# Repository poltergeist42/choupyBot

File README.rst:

=========
choupyBot
=========

   :Autheur:          `Poltergeist42 <https://github.com/poltergeist42>`_
   :Organistation:    `VoLAB <https://github.com/volab>`_
   :Projet:           `choupyBot <https://github.com/volab/choupyBot>`_
   :Licence:          CC BY-NC-SA 4.0
   :Liens:            https://creativecommons.org/licenses/by-nc-sa/4.0/ 

------------------------------------------------------------------------------------------

Description
===========

ChoupyBot est un petit "robot" animé par un Raspberry pi et motoriser par 2 moteurs
pas à pas (PAP) et un capteur ultrason.

L'objectif de ce projet et de réaliser une petite plateforme ludique qui pourra être
programmée / commandée à distance par un enfant. Ce robot évoluera dans un quadrillage
de 15x15.

**N.B :** la dimension des cases sera déterminée ultérieurement en fonction
de la taille du robot.

Voir le doc de conception pour plus de détail :
https://github.com/volab/choupyBot/blob/master/_1_userDoc/choupyBot_doc.rst

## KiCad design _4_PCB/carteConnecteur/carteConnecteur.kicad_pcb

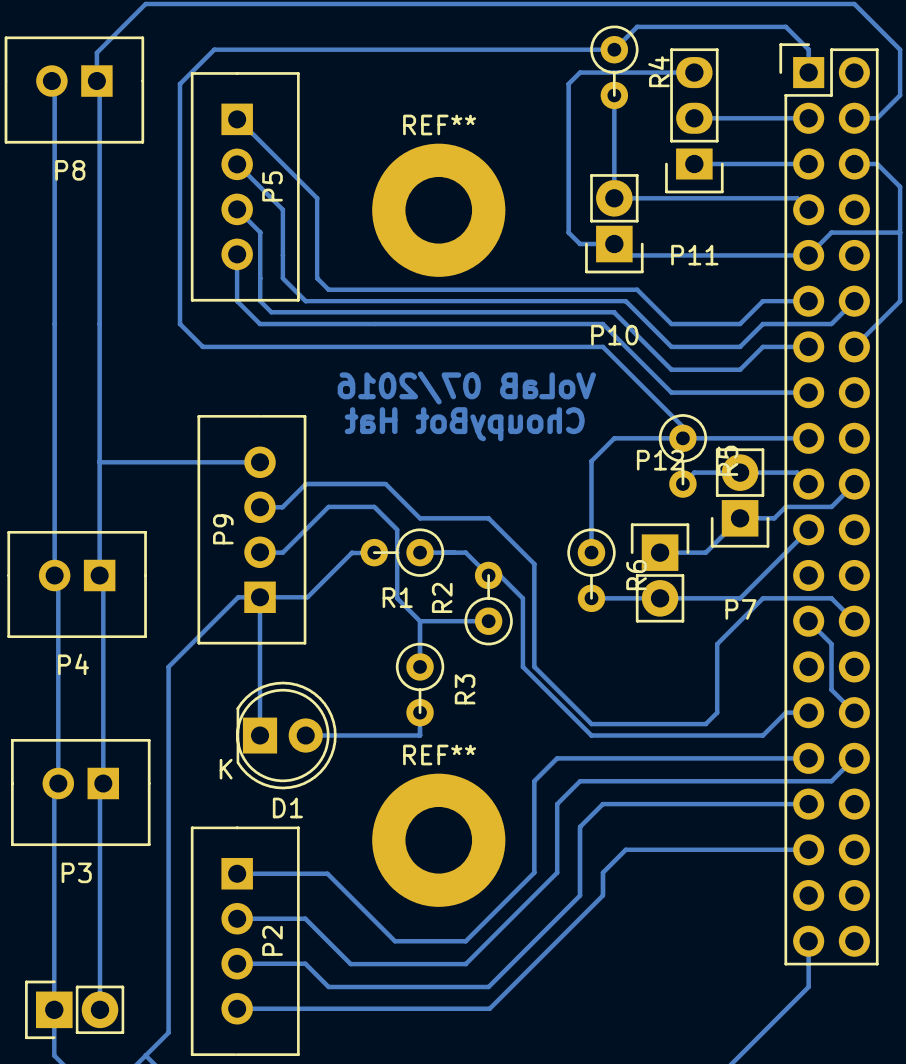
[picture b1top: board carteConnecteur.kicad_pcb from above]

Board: 2 copper layers, 19 parts (0 on the bottom side), 20 nets.

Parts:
D1: LED; LED-5MM
P1: +5 (ubec); Pin_Header_Straight_1x02
P2: PAP_D; XH_connector_4pins_Vert
P3: +5 (pap_G); XH_connector_2pins_Vert
P4: +5 (pap_D); XH_connector_2pins_Vert
P5: PAP_G; XH_connector_4pins_Vert
P6: RPi_Conn; Pin_Header_Straight_2x20
P7: BP1; Pin_Header_Straight_1x02
P8: +5 (RPi); XH_connector_2pins_Vert
P9: HC-SR04; XH_connector_4pins_Vert
P10: N.U; Pin_Header_Straight_1x02
P11: I2c; Pin_Header_Straight_1x03
P12: BP2; Pin_Header_Straight_1x02
R1: 20k; Resistor_Vertical_2-54
R2, R4, R5, R6: 10k; Resistor_Vertical_2-54
R3: 330R; Resistor_Vertical_2-54

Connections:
+3V3: P6.1, P6.17, R4.1, R5.1, R6.1
/Echo: P9.2, R2.1, R3.1
/GPIO04: P6.7, P10.2, R4.2
/GPIO06: P2.1, P6.31
/GPIO12: P2.2, P6.32
/GPIO13: P2.3, P6.33
/GPIO17: P5.1, P6.11
/GPIO18: P5.2, P6.12
/GPIO19: P2.4, P6.35
/GPIO22: P5.4, P6.15
/GPIO27: P5.3, P6.13
/SCL: P6.5, P11.1
/SDA: P6.3, P11.2
/Trig: P6.26, P9.3
GNDPWR: D1.1, P1.1, P3.2, P4.2, P6.6, P6.9, P6.14, P6.20, P6.25, P6.30, P6.39, P7.1, P8.2, P9.1, P10.1, P11.3, P12.1, R1.2
unnamed: D1.2, R3.2
unnamed: P6.19, P7.2, R5.2
unnamed: P6.29, R1.1, R2.2
unnamed: P6.21, P12.2, R6.2
VCC: P1.2, P3.1, P4.1, P6.4, P8.1, P9.4

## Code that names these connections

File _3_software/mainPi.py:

#!/usr/bin/env python
# -*- coding: utf-8 -*-

"""

=========
choupyBot
=========

   :Nom du fichier:     choupyBot.py
   :Autheur:            `Poltergeist42 <https://github.com/poltergeist42>`_
   :Version:            20160731

####

   :Licence:            CC-BY-NC-SA
   :Liens:              https://creativecommons.org/licenses/by-nc-sa/4.0/

####

    :dev language:      Python 3.4
    
####

lexique
=======

   :**v_**:                 variable
   :**l_**:                 list
   :**t_**:                 tuple
   :**d_**:                 dictionnaire
   :**f_**:                 fonction
   :**C_**:                 Class
   :**i_**:                 Instance
   :**m_**:                 Module
"""
try :
    from moteurPap.moteurPap import C_MoteurPap
except ImportError :
    print( "module 'moteurPap' non charge") 

try :
    from ultrason.ultrason import C_ultrasonSensor
except ImportError :
    print( "module 'ultrason' non charge")
    
try :
    from devChk.devChk import C_DebugMsg
except ImportError :
    print( "module 'devChk' non charge")
    
try :
    from objJson.objJson import C_ObjJson
except ImportError :
    print( "module 'objJson' non charge")

class C_choupyBot(object) :
    def __init__(self, ):
        """ variables globales """
        
        ## Creation de l'instance de C_DebugMsg
        self.i_dbg = C_DebugMsg()
        
        ## Variables globales
        self.v_case = 15
        self.v_mode = ""
        
        
        
    def __del__(self) :
        """ Destructor
        
            Permet de fremer proprement l'instance en cours.
            il faut utilise :
            ::
            
                del [nom_de_l'_instance]
                
            N.B : cette methode est appelee automatiquement par le ramasse miette si
            l'instance n'est plus solicitee.
        """
        v_className = self.__class__.__name__
        print("\n\t\tL'instance de la class {} est terminee".format(c_className))

        
    def f_setMode(self, v_mode = "boxxle") :
        """ identification / modification du mode de fonctionnement du robot
        
            Le Robot peut être parametrer pour fonctionner selon plusieur mode.
            
            **Les modes disponibles sont :**
            
                * Boxxle (mode par defaut)
                * Parcours
                * Aventure
        """
        if v_mode == "boxxle" or v_mode == "parcours" or v_mode == "aventure"
            self.v_mode = v_mode
        else : self.v_mode = "boxxle"
        
    def f_papInit(self):
        """ initialisation des 2 moteur pas a pas (pap)
        
            +------------+-------------------------+
            | BCM (GPIO) | Serigraphie sur UNL2003 |
            +============+=========================+
            |   v_gpioA  |           N1            |
            +------------+-------------------------+
            |   v_gpioB  |           N2            |
            +------------+-------------------------+
            |   v_gpioC  |           N3            |
            +------------+-------------------------+
            |   v_gpioD  |           N4            |
            +------------+-------------------------+
           
            le papGauche est intialiser sur les GPIO par defaut soit ::
           
                v_gpioA = GPIO17
                v_gpioB = GPIO18
                v_gpioC = GPIO27
                v_gpioD = GPIO22
           
            et tourne dans le sens anti-horriare.
            le papDroit est initialiser sur un autre jeux de GPIO ::
           
                v_gpioA = GPIO06
                v_gpioB = GPIO12
                v_gpioC = GPIO13
                v_gpioD = GPIO19
                
            et tourne dans le sens horriare. La valeur de v_rayonInit correspond
            au rayon des roues du robot. Les deux pap tournes en sens inverse l'un de 
            l'aure, pour que le robot puisse aller tout droit.
        """
       
        ## papGauche
        self.i_papGauche = C_MoteurPap(v_rotationInit = "antihorraire", v_rayonInit = 3)
        self.i_papGauche.f_gpioInit(v_gpioA=06, v_gpioB=12, v_gpioC=13, v_gpioD=19)
        
        ## papDroit
        self.i_PapDroit  = C_MoteurPap(v_rayonInit = 3)
        self.i_PapDroit.f_gpioInit()

                                        
    def f_sonarInit(self) :
        """ Initialisation du capteur ultrason

        La broche du trig et configuer sur GPIO 7 par défaut.
        La broche echo ayant le GPIO 12 par defaut, elle a ete reconfiguree
        sur GPIO 5
        """
        
        i_ultrason = C_ultrasonSensor()
        i_ultrason.f_ultraInit(v_gpioEcho = 5)
    
    def f_avance(self) :
        """ avance tout droit """
        
    def f_recul(self) :
        """ reculler tout droit """
        
    def f_gauche(self) :
        """ tourner a gauche """
        
    def f_droite(self) :
        """ Tourner a droite """

def main() :
    """ Fonction principal """
    i_choupy = C_choupyBot()
    i_choupy.f_papInit()
    i_choupy.f_sonarInit()

    
    
if __name__ == '__main__':
    main()

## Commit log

2016-06-08 ajout de "VoLAB.rst" a la racine de l'arbo
2016-06-11 Creation de la bibliotheque 'ultrason'
2016-06-11 creation de 'choupyBot_doc.rst'
2016-06-12 preparation des fonctions de deplacement dans 'mainPi'
2016-06-12 complement du descriptif detaille Changes to be committed: modified: 01_userDoc/choupyBot_doc.rst
2016-06-12 ajout de la fonction "f_sensDeRotation" modified: 03_software/moteurPap.py
2016-06-12 factorisation de la sequence de mouvement des PAP
2016-06-12 Ajout des fonctions de conversion des cm en deg et en step
2016-06-12 ajout du destructor '__del__', ajout d'une fonction main pour les test
2016-06-12 ajout de la methode '__del__' et d'une fonction 'main' dans ultrason.py
2016-07-04 modification des noms de l'arborescence
2016-07-06 ajout des lib 'devChk', 'moteurPap' et 'ultrason'
2016-07-06 ajout de la methode 'f_sonarInit'
2016-07-11 ajout de la fonction 'f_setMode' dans 'mainPi'
2016-07-14 modelisation du robot sous fusion 360 + mise a dispo des sources et des STL
2016-07-15 modif mineur dans le doc de conception
2016-07-20 conception du PCB
2016-07-20 modif mineur sur '.gitignore'
2016-07-20 ajout de la liste des composant dans le doc de conception
2016-07-20 complement de la liste de materiel
2016-07-21 complement du doc de conception : 'choupyBot_doc.rst'
2016-07-31 ajout de 3 connecteur + pull-up sur le PCB + mise à jour des libs dans 'software'
